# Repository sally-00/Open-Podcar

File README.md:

# Open Podcar 2.0

This is a project extended from [OpenPodcar](https://github.com/OpenPodcar/OpenPodcar).

We have changed components and improved the PCB layout to allow more flexibility in the system and ensure safty while operating the car.

At current stage, we have tested the linear actuator, almost finished the design of PCB except a few further improvements.
We will mount the linear actuator, manufactor the PCB and mount all the components in the close future.

## Linear Actuator Demostration
A demostration of controlling the linear actuator with the joystick which pass the steer command to the ESP32 through ROS using Wi-Fi is shown as follows.

## PCB design
The final schematic of the PCB is shown as follows.

The layout of the PCB at the current stage is shown as follows.

## Bill of Materials

#### Vehicle
1 Gimson Robotics GLA750-P 12V DC linear actuator with position feedback (100mm stroke)

Metal bracket [linik to product](https://www.amazon.co.uk/dp/B08JV76967?ref_=cm_sw_r_apin_dp_HXTQEXMHK0DS5XG23BHY)

#### PCB

1 ESP32 [link to product](https://www.amazon.co.uk/XTVTX-Development-Wireless-Bluetooth-Frequency/dp/B09LCDJY8Z/ref=sr_1_5?crid=2XLMJ0XECAAJR&keywords=esp32&qid=1669377505&s=industrial&sprefix=esp32%2Cindustrial%2C95&sr=1-5)

1 DollaTek BTS7960 5.5V to 27V 43A High Power Motor Driver [link to product](https://www.amazon.co.uk/gp/product/B09H6MKWCJ/ref=ppx_yo_dt_b_asin_title_o00_s00?ie=UTF8&psc=1)

1 Digital to Analog Converter [link to product](https://www.digikey.co.uk/en/products/detail/sparkfun-electronics/BOB-12918/5140812?utm\_adgroup=Evaluation%20Boards%20-%20Digital%20to%20Analog%20Converters%20%28DACs%29&utm\_source=google&utm\_medium=cpc&utm\_campaign=Shopping\_Product\_Development%20Boards%2C%20Kits%2C%20Programmers&utm\_term=&productid=5140812&gclid=CjwKCAiAs8acBhA1EiwAgRFdw7jZpmNLCZSMikVMd7oKKiSc0wkz7JpF8sl4ogsQpp6ZFNUjAHO2KBoC\_PIQAvD_BwE)

1 Buck Converter Module 24V to 12V 15A [link to product](https://www.amazon.co.uk/dp/B01KQWWSLA/)

1 Buck Converter Module 12V to 5V 5A [link to product](https://www.amazon.co.uk/dp/B09NVZ6Y6J?ref_=cm\_sw\_r\_apin\_dp_F5CDBP8B0AESHGP8G7D0)

JST-XH connector [link to product](https://www.amazon.co.uk/YIXISI-460Pcs-Housing-Connector-Adapter/dp/B082ZLYRRN/ref=asc_df_B082ZLYRRN/?tag=googshopuk-21&linkCode=df0&hvadid=394317030617&hvpos=&hvnetw=g&hvrand=13959213679084324666&hvpone=&hvptwo=&hvqmt=&hvdev=m&hvdvcmdl=&hvlocint=&hvlocphy=1006876&hvtargid=pla-928147660517&psc=1&tag=&ref=&adgrpid=80755971054&hvpone=&hvptwo=&hvadid=394317030617&hvpos=&hvnetw=g&hvrand=13959213679084324666&hvqmt=&hvdev=m&hvdvcmdl=&hvlocint=&hvlocphy=1006876&hvtargid=pla-928147660517)

Male XT60PW Gold Plated connector [link to product](https://www.switchelectronics.co.uk/male-xt60pw-gold-plated-connector-30a-amass?gclid=Cj0KCQiAqOucBhDrARIsAPCQL1Z9Mdg7JQ2CPNNQ3Sm97k74ZDQKxPksRo_lDsgrQek7YlSQR7QdGtQaAu9BEALw_wcB)

XT-60H connector [link to product](https://amzn.eu/d/4VwUmz3)

Fuse holder [link to product](https://uk.farnell.com/littelfuse/178-7017-0001/fuse-holder-pcb-r-a-blade/dp/310530?st=Ato%20fuse%20holder)

5A Fuse

10A Fuse

Potentiometer [link to product](https://uk.rs-online.com/web/p/potentiometers/8274990?cm_mmc=UK-PLA-DS3A-_-google-_-CSS_UK_EN_Passive_Components_MOB_Whoop-_-Potentiometers_Whoop-_-8274990&matchtype=&pla-346415135252&cq_src=google_ads&cq_cmp=9765532007&cq_term=&cq_plac=&cq_net=g&cq_plt=gp&gclid=CjwKCAiAv9ucBhBXEiwA6N8nYOlC97hC1rk_lZlzGOEZ-jXB8kbkuMIexTun0_bgiT8PpbOJ3vPO0hoCik4QAvD_BwE&gclsrc=aw.ds)

Jumper wire [link to product](https://www.amazon.co.uk/VIPMOON-1-17mm-Multicolored-Flexible-Rainbow/dp/B07BLRNTXW/ref=asc_df_B07BLRNTXW/?tag=googshopuk-21&linkCode=df0&hvadid=309903005216&hvpos=&hvnetw=g&hvrand=16844014482739590557&hvpone=&hvptwo=&hvqmt=&hvdev=m&hvdvcmdl=&hvlocint=&hvlocphy=1006876&hvtargid=pla-631740601899&psc=1)

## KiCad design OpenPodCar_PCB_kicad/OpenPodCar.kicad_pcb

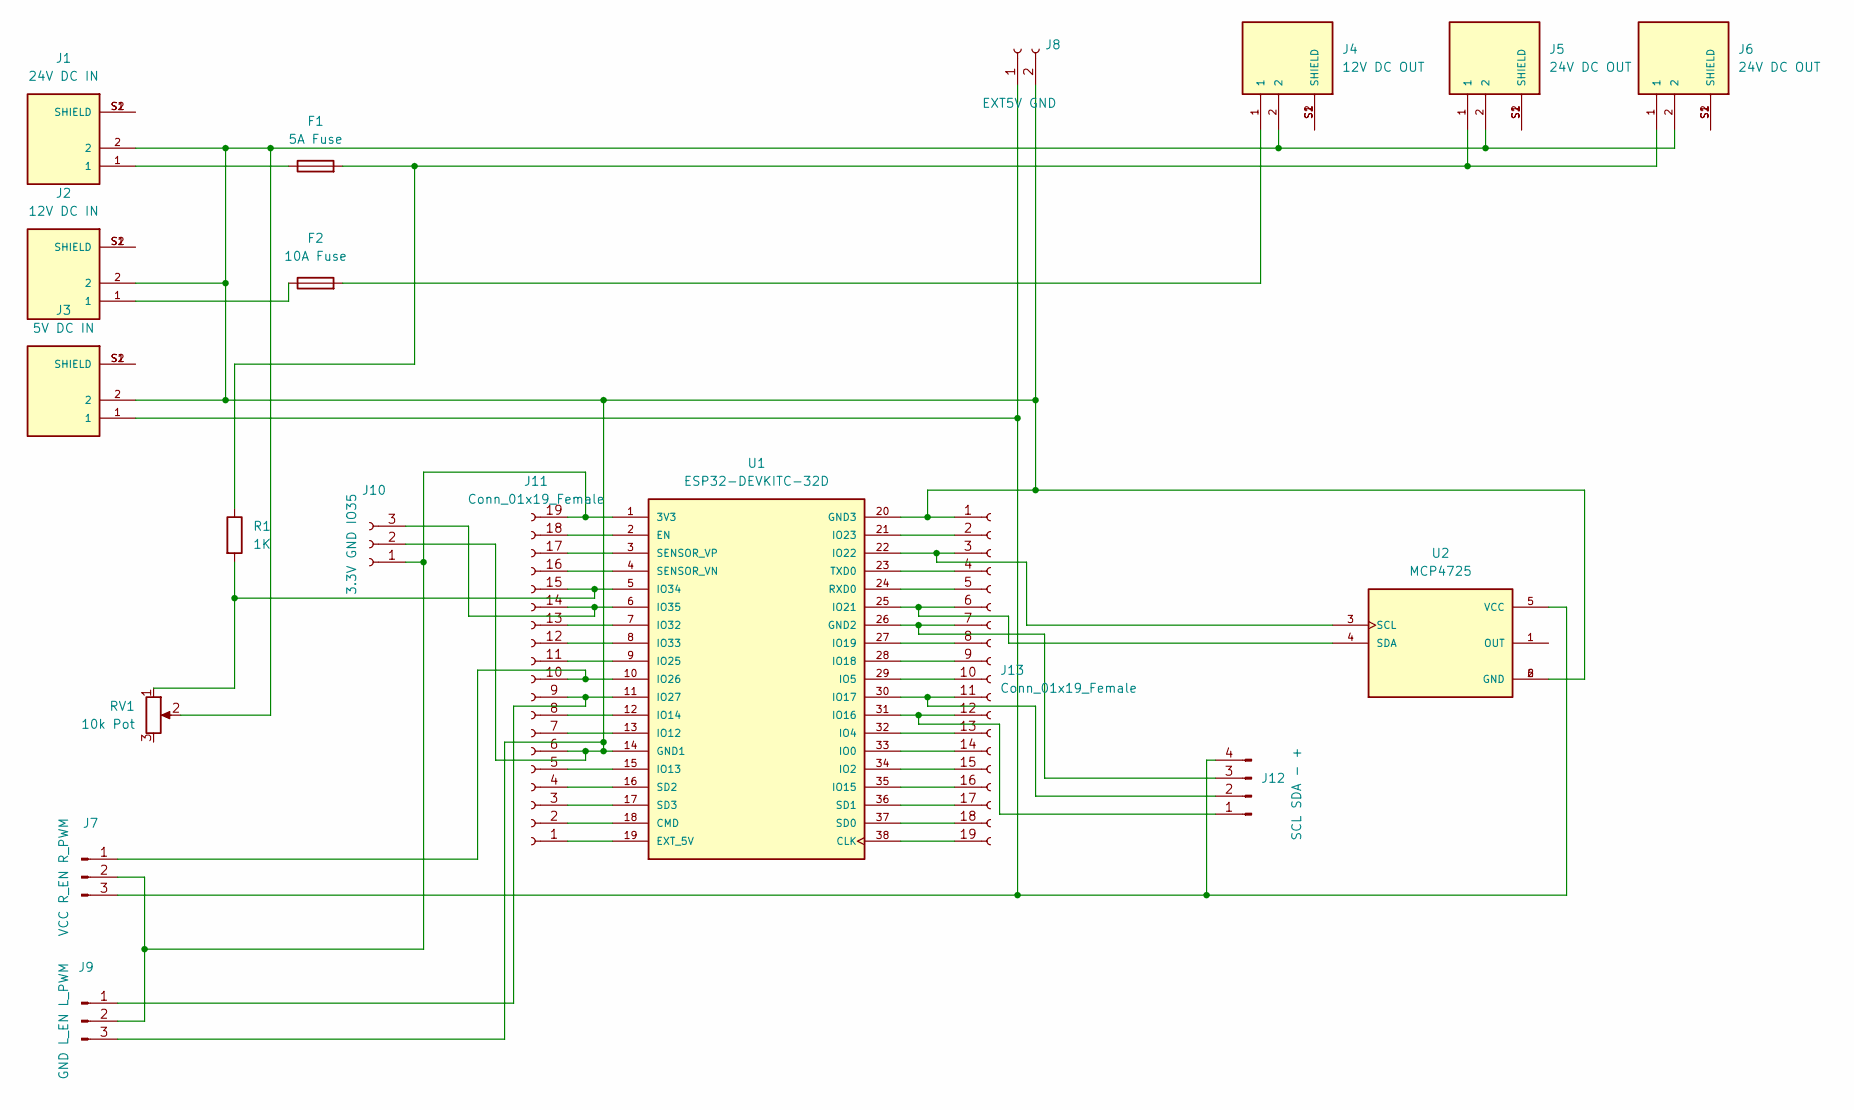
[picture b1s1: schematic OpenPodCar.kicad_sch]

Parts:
F1: 5A Fuse; Fuseholder_Blade_ATO_Littelfuse_Pudenz_2_Pin
F2: 10A Fuse; Fuseholder_Blade_ATO_Littelfuse_Pudenz_2_Pin
J1: 24V DC IN; AMASS_XT60PW-F; PARTREV V1.2
J2: 12V DC IN; AMASS_XT60PW-F; PARTREV V1.2
J3: 5V DC IN; AMASS_XT60PW-F; PARTREV V1.2
J4: 12V DC OUT; AMASS_XT60PW-F; PARTREV V1.2
J5, J6: 24V DC OUT; AMASS_XT60PW-F; PARTREV V1.2
J7: VCC R_EN R_PWM; JST_XH_B3B-XH-A_1x03_P2.50mm_Vertical
J8: EXT5V GND; JST_XH_B2B-XH-A_1x02_P2.50mm_Vertical
J9: GND L_EN L_PWM; JST_XH_B3B-XH-A_1x03_P2.50mm_Vertical
J10: 3.3V GND IO35; JST_XH_B3B-XH-A_1x03_P2.50mm_Vertical
J11, J13: Conn_01x19_Female; PinHeader_1x19_P2.54mm_Vertical
J12: SCL SDA - +; PinHeader_1x04_P2.54mm_Vertical
R1: 1K; R_Axial_DIN0207_L6.3mm_D2.5mm_P7.62mm_Horizontal
RV1: 10k Pot; Potentiometer_Bourns_PTV09A-1_Single_Vertical
U1: ESP32-DEVKITC-32D; MODULE_ESP32-DEVKITC-32D; PARTREV 4
U2: MCP4725; MODULE_ZC576300; PARTREV v14

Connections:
unnamed: F1.1, J1.1
unnamed: F1.2, J5.1, J6.1, R1.1
unnamed: F2.1, J2.1
unnamed: F2.2, J4.1
unnamed: J1.2, J2.2, J3.2, J4.2, J5.2, J6.2, J8.2, J9.3, J10.2, J11.6, J13.1, RV1.2, U1.14 (GND1), U1.20 (GND3), U2.2 (GND), U2.6 (GND)
unnamed: J1.S1 (SHIELD), J1.S2 (SHIELD)
unnamed: J2.S1 (SHIELD), J2.S2 (SHIELD)
unnamed: J3.S1 (SHIELD), J3.S2 (SHIELD)
unnamed: J4.S1 (SHIELD), J4.S2 (SHIELD)
unnamed: J5.S1 (SHIELD), J5.S2 (SHIELD)
unnamed: J6.S1 (SHIELD), J6.S2 (SHIELD)
unnamed: J7.2, J9.2, J10.1, J11.19, U1.1 (3V3)
unnamed: J10.3, J11.14, U1.6 (IO35)
unnamed: J11.1, U1.19 (EXT_5V)
unnamed: J11.2, U1.18 (CMD)
unnamed: J11.3, U1.17 (SD3)
unnamed: J11.4, U1.16 (SD2)
unnamed: J11.5, U1.15 (IO13)
unnamed: J11.7, U1.13 (IO12)
unnamed: J11.8, U1.12 (IO14)
unnamed: J9.1, J11.9, U1.11 (IO27)
unnamed: J7.1, J11.10, U1.10 (IO26)
unnamed: J11.11, U1.9 (IO25)
unnamed: J11.12, U1.8 (IO33)
unnamed: J11.13, U1.7 (IO32)
unnamed: J11.15, R1.2, RV1.1, U1.5 (IO34)
unnamed: J11.16, U1.4 (SENSOR_VN)
unnamed: J11.17, U1.3 (SENSOR_VP)
unnamed: J11.18, U1.2 (EN)
unnamed: J12.1, J13.12, U1.31 (IO16)
unnamed: J12.2, J13.11, U1.30 (IO17)
unnamed: J12.3, J13.7, U1.26 (GND2)
unnamed: J3.1, J7.3, J8.1, J12.4, U2.5 (VCC)
unnamed: J13.2, U1.21 (IO23)
unnamed: J13.3, U1.22 (IO22), U2.3 (SCL)
unnamed: J13.4, U1.23 (TXD0)
unnamed: J13.5, U1.24 (RXD0)
unnamed: J13.6, U1.25 (IO21), U2.4 (SDA)
unnamed: J13.8, U1.27 (IO19)
unnamed: J13.9, U1.28 (IO18)
unnamed: J13.10, U1.29 (IO5)
unnamed: J13.13, U1.32 (IO4)
unnamed: J13.14, U1.33 (IO0)
unnamed: J13.15, U1.34 (IO2)
unnamed: J13.16, U1.35 (IO15)
unnamed: J13.17, U1.36 (SD1)
unnamed: J13.18, U1.37 (SD0)
unnamed: J13.19, U1.38 (CLK)

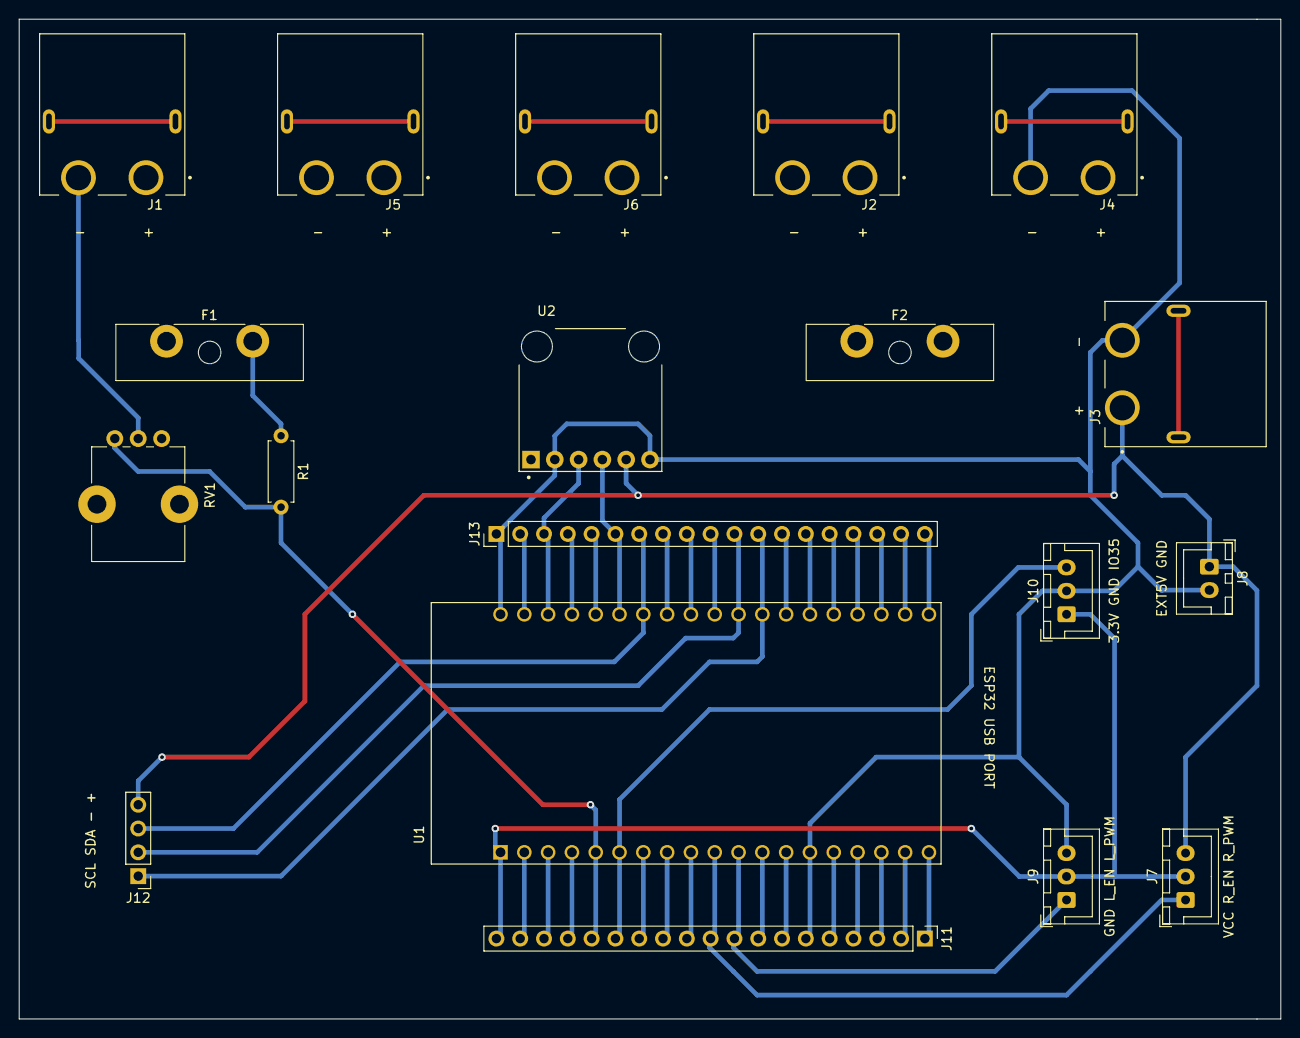
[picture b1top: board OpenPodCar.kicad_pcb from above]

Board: 2 copper layers, 134.6 x 106.7 mm, 19 parts (0 on the bottom side), 48 nets.

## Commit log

2023-01-22 added option for switching ROS off
2023-01-22 added ROS code used on linux computer
2023-01-22 added README
2023-01-23 edited README
2023-01-26 added PCB files
2023-01-26 publish cmd in joystick
2023-01-26 ESP32 linear actuator reading adjustment, ros msg receive adjustment
2023-01-26 added skematics and demostration in README
2023-01-26 changed movie file extention
2023-01-26 publish battery voltage
2023-01-31 update PCB
2023-02-02 update README steer test
2023-02-04 Added voltage display
